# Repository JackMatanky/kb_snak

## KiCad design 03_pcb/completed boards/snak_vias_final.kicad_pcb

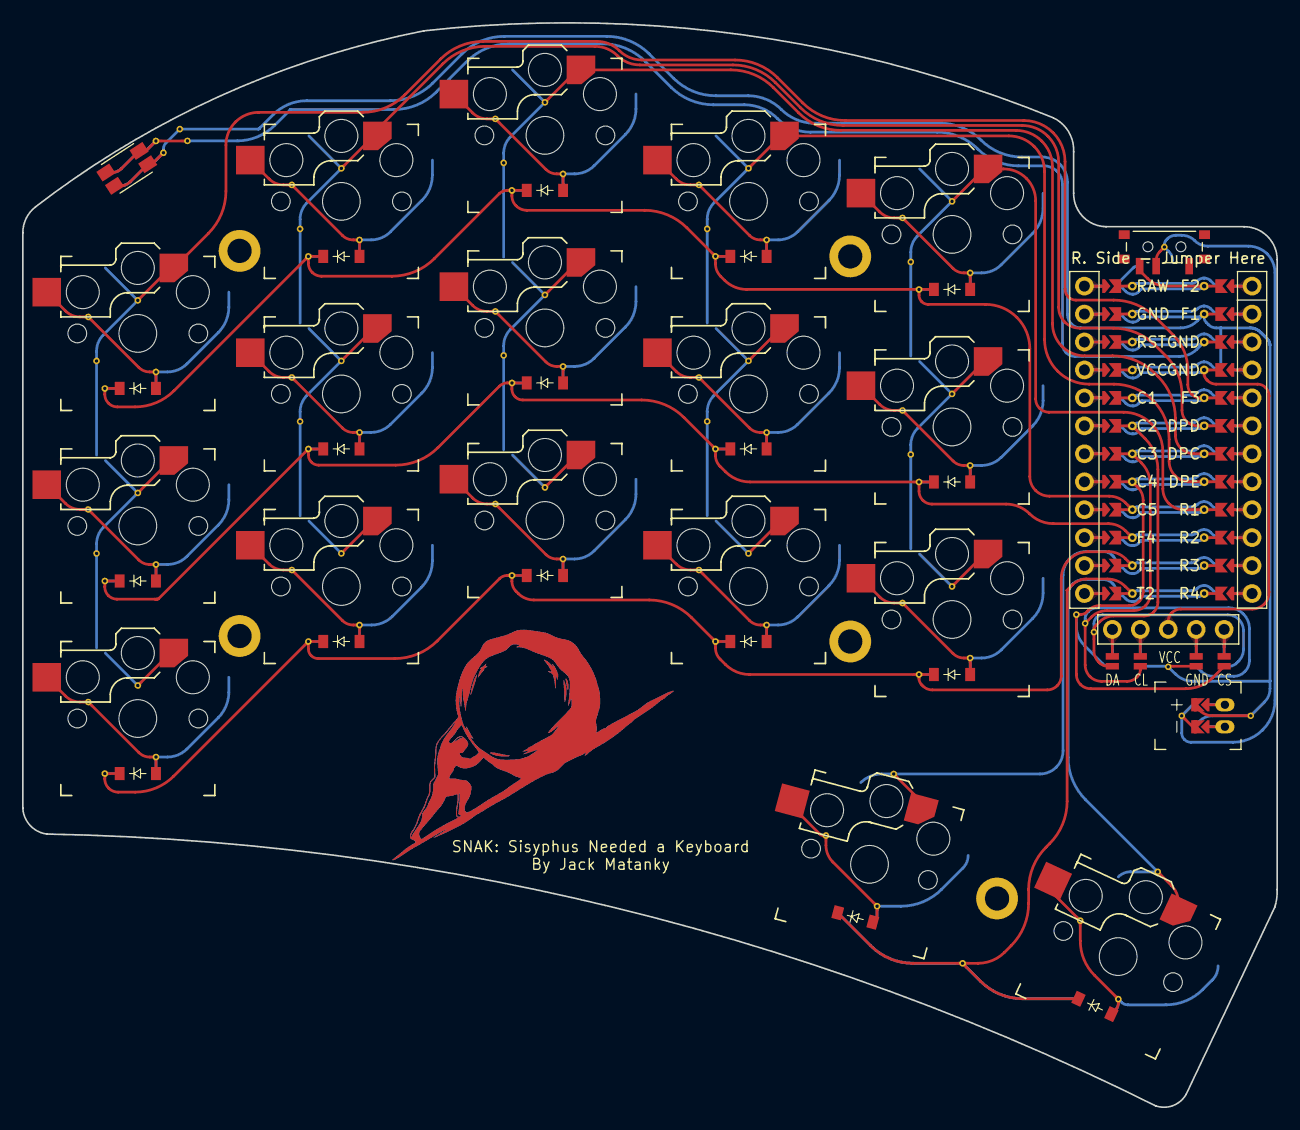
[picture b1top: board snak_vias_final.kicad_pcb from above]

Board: 2 copper layers, 114.0 x 98.6 mm, 44 parts (0 on the bottom side), 42 nets.

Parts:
D1, D2, D3, D4, D5, D6, D7, D8, D9, D10, D11, D12, D13, D14, D15, D16, D17: ComboDiode
DISP1: nice!view
H1, H2, H3, H4, H5: mounting_hole
JST1: JST_PH_S2B-PH-K
MCU1: nice_nano
S1, S2, S3, S4, S5, S6, S7, S8, S9, S10, S11, S12, S13, S14, S15, S16, S17: PG1350
SW1: power_switch
SW2: sw_reset_side

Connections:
C1: MCU1.5, S1.1, S2.1, S3.1
C2: MCU1.6, S4.1, S5.1, S6.1
C3: MCU1.7, S7.1, S8.1, S9.1
C4: MCU1.8, S10.1, S11.1, S12.1
C5: MCU1.9, S13.1, S14.1, S15.1
DISP1_1: DISP1.1, DISP1.14, DISP1.27
DISP1_2: DISP1.2, DISP1.15, DISP1.26
DISP1_4: DISP1.4, DISP1.16, DISP1.25
DISP1_5: DISP1.5, DISP1.17, DISP1.24
DPC: DISP1.11, DISP1.21, MCU1.118
DPD: DISP1.10, DISP1.20, MCU1.119
DPE: DISP1.13, DISP1.23, MCU1.117
GND: DISP1.12, DISP1.22, JST1.1, MCU1.2, MCU1.121, MCU1.122, SW2.1
JST1_1: JST1.11, JST1.21, JST1.31
JST1_2: JST1.12, JST1.22, JST1.32
R1: D3.1, D6.1, D9.1, D12.1, D15.1, MCU1.116
R2: D2.1, D5.1, D8.1, D11.1, D14.1, MCU1.115
R3: D1.1, D4.1, D7.1, D10.1, D13.1, MCU1.114
R4: D16.1, D17.1, MCU1.113
RAW: MCU1.1, SW1.3, SW1.6
RST: MCU1.3, SW2.2
T1: MCU1.11, S16.1
T2: MCU1.12, S17.1
VCC: DISP1.3, MCU1.4
in_home: D17.2, S17.2
index_bot: D10.2, S10.2
index_mid: D11.2, S11.2
index_top: D12.2, S12.2
inner_bot: D13.2, S13.2
inner_mid: D14.2, S14.2
inner_top: D15.2, S15.2
middle_bot: D7.2, S7.2
middle_mid: D8.2, S8.2
middle_top: D9.2, S9.2
out_home: D16.2, S16.2
pinky_bot: D1.2, S1.2
pinky_mid: D2.2, S2.2
pinky_top: D3.2, S3.2
pos: JST1.2, SW1.2, SW1.5
ring_bot: D4.2, S4.2
ring_mid: D5.2, S5.2
ring_top: D6.2, S6.2
